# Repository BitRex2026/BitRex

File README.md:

Bitcoin Miner With 4 BM1373 Chips

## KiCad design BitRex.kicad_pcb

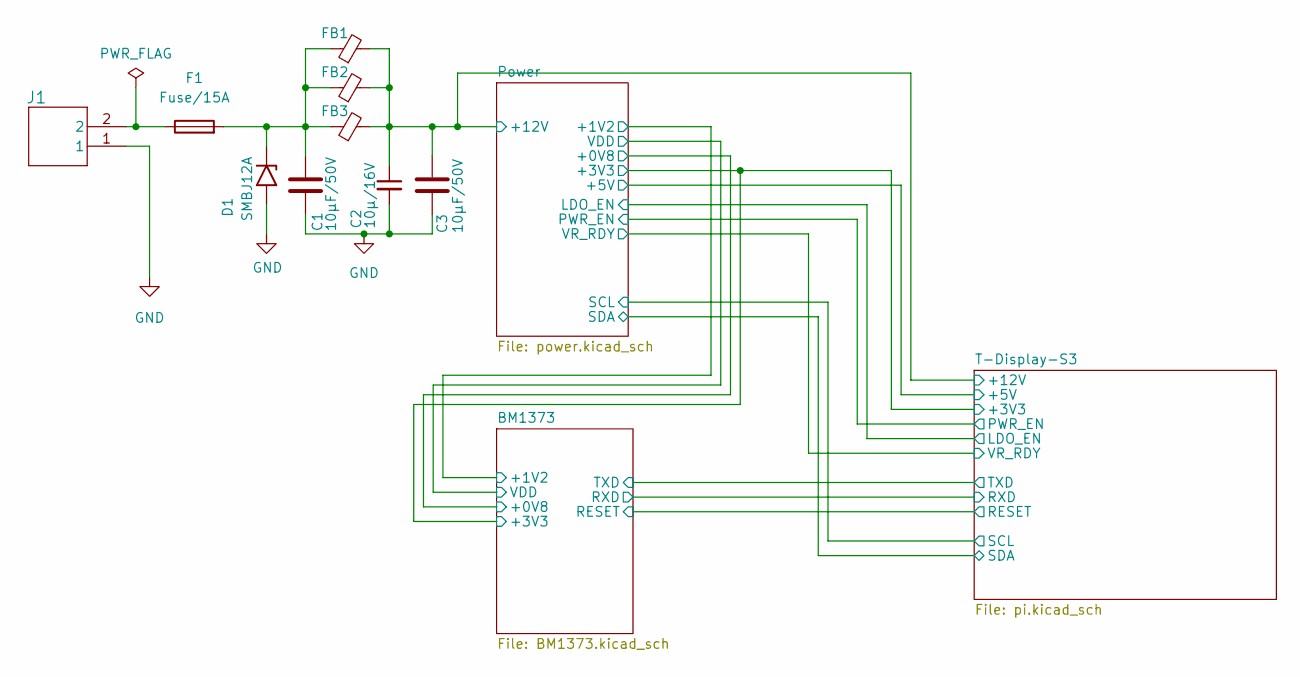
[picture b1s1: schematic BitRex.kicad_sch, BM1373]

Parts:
C1, C3: 10µF/50V; C_1206_3216Metric
C2: 10µ/16V; C_0603_1608Metric
D1: SMBJ12A; D_SMB; LCSC C113985
F1: Fuse/15A; Fuseholder_Blade_Mini_Keystone_3568
FB1, FB2, FB3: BLE32SN120SN1L; R_1210_3225Metric_Pad1.30x2.65mm_HandSolder; LCSC C5597997
J1: Connector 02x01; AMASS_XT60PW-M_1x02_P7.20mm_Horizontal; LCSC C98732

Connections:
+12V: C2.1, C3.1, FB1.2, FB2.2, FB3.2; also elsewhere on the board
GND: C1.2, C2.2, C3.2, D1.2 (A2), J1.1; also elsewhere on the board
unnamed: C1.1, D1.1 (A1), F1.2, FB1.1, FB2.1, FB3.1
unnamed: F1.1, J1.2

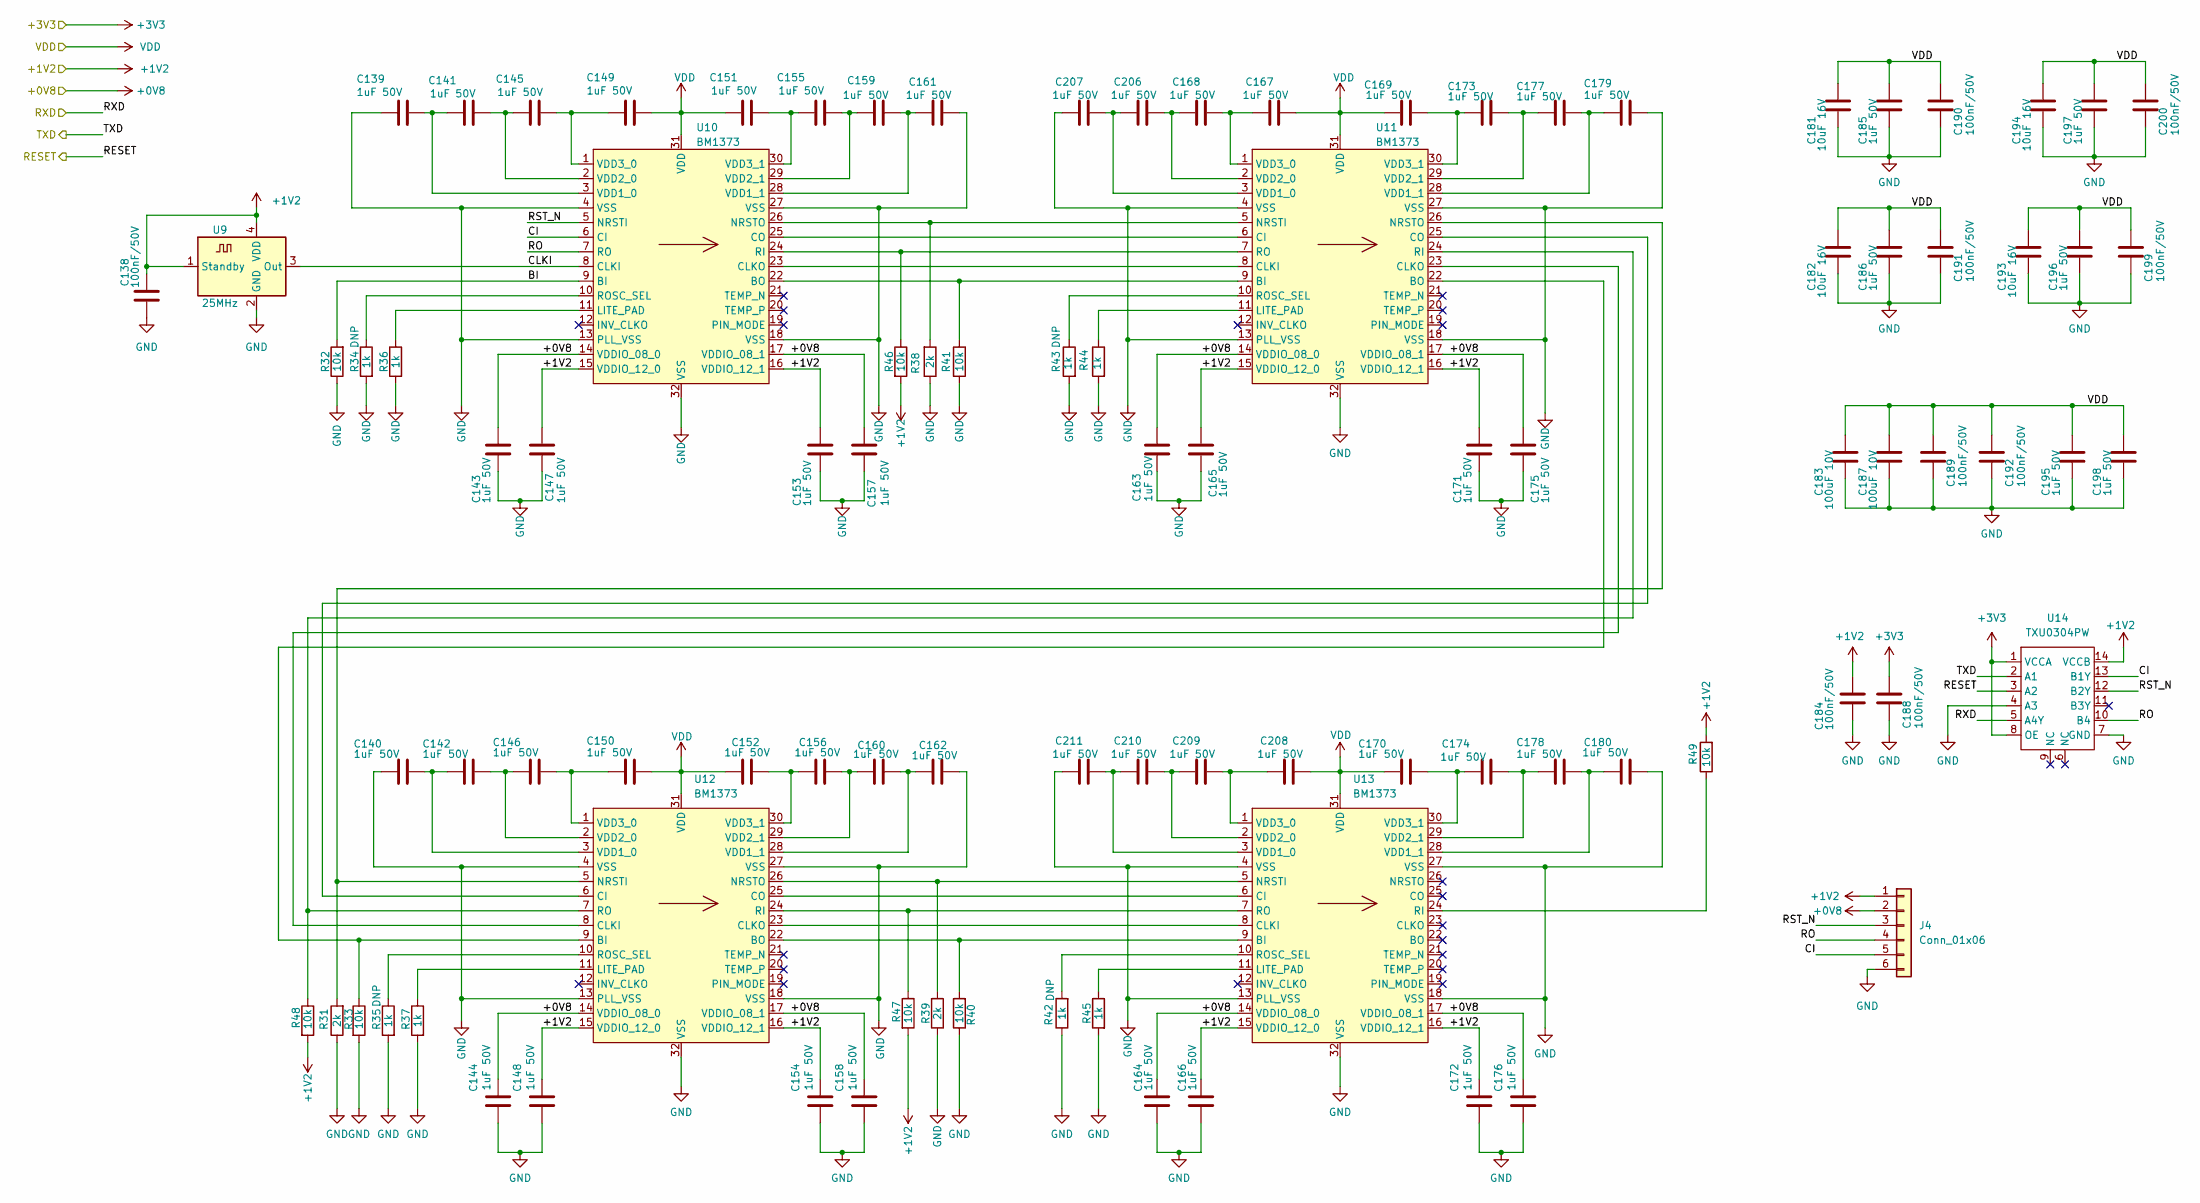
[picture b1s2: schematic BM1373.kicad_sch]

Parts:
C138, C184, C188, C189, C190, C191, C192, C199, C200: 100nF/50V; C_0805_2012Metric
C139, C140, C141, C142, C143, C144, C145, C146, C147, C148, C149, C150, C151, C152, C153, C154, C155, C156, C157, C158, C159, C160, C161, C162, C163, C164, C165, C166, C167, C168, C169, C170, C171, C172, C173, C174, C175, C176, C177, C178, C179, C180, C185, C186, C195, C196, C197, C198, C206, C207, C208, C209, C210, C211: 1uF 50V; C_0805_2012Metric
C181, C182, C193, C194: 10uF 16V; C_0805_2012Metric
C183, C187: 100uF 10V; C_1206_3216Metric
J4: Conn_01x06; PinHeader_1x06_P1.27mm_Vertical
R31, R38, R39: 2k; R_0603_1608Metric
R32, R33, R40, R41, R46, R47, R48, R49: 10k; R_0603_1608Metric
R34, R35, R36, R37, R42, R43, R44, R45: 1k; R_0603_1608Metric
U9: 25MHz; Oscillator_SMD_EuroQuartz_XO32-4Pin_3.2x2.5mm
U10, U11, U12, U13: BM1373; BM1373CC
U14: TXU0304PW; TSSOP-14_4.4x5mm_P0.65mm

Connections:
+0V8: C143.1, C144.1, C157.1, C158.1, C163.1, C164.1, C175.1, C176.1, J4.2, U10.14 (VDDIO_08_0), U10.17 (VDDIO_08_1), U11.14 (VDDIO_08_0), U11.17 (VDDIO_08_1), U12.14 (VDDIO_08_0), U12.17 (VDDIO_08_1), U13.14 (VDDIO_08_0), U13.17 (VDDIO_08_1); also elsewhere on the board
+1V2: C138.1, C147.1, C148.1, C153.1, C154.1, C165.1, C166.1, C171.1, C172.1, C184.1, J4.1, R46.2, R47.2, R48.2, R49.2, U9.1 (Standby), U9.4 (VDD), U10.15 (VDDIO_12_0), U10.16 (VDDIO_12_1), U11.15 (VDDIO_12_0), U11.16 (VDDIO_12_1), U12.15 (VDDIO_12_0), U12.16 (VDDIO_12_1), U13.15 (VDDIO_12_0), U13.16 (VDDIO_12_1), U14.14 (VCCB); also elsewhere on the board
+3V3: C188.1, U14.1 (VCCA), U14.8 (OE); also elsewhere on the board
/BM1373/BI: R32.2, U10.9 (BI)
/BM1373/CI: J4.5, U10.6 (CI), U14.13 (B1Y)
/BM1373/CLKI: U9.3 (Out), U10.8 (CLKI)
/BM1373/RESET: U14.3 (A2); also elsewhere on the board
/BM1373/RO: J4.4, U10.7 (RO), U14.10 (B4)
/BM1373/RST_N: J4.3, U10.5 (NRSTI), U14.12 (B2Y)
/BM1373/RXD: U14.5 (A4Y); also elsewhere on the board
/BM1373/TXD: U14.2 (A1); also elsewhere on the board
GND: C138.2, C139.1, C140.1, C143.2, C144.2, C147.2, C148.2, C153.2, C154.2, C157.2, C158.2, C161.2, C162.2, C163.2, C164.2, C165.2, C166.2, C171.2, C172.2, C175.2, C176.2, C179.2, C180.2, C181.1, C182.1, C183.1, C184.2, C185.1, C186.1, C187.1, C188.2, C189.2, C190.2, C191.2, C192.2, C193.1, C194.1, C195.1, C196.1, C197.1, C198.1, C199.2, C200.2, C207.1, C211.1, J4.6, R31.1, R32.1, R33.2, R34.2, R35.2, R36.2, R37.2, R38.1, R39.1, R40.1, R41.2, R42.1, R43.2, R44.2, R45.2, U9.2 (GND), U10.4 (VSS), U10.13 (PLL_VSS), U10.18 (VSS), U10.27 (VSS), U10.32 (VSS), U11.4 (VSS), U11.13 (PLL_VSS), U11.18 (VSS), U11.27 (VSS), U11.32 (VSS), U12.4 (VSS), U12.13 (PLL_VSS), U12.18 (VSS), U12.27 (VSS), U12.32 (VSS), U13.4 (VSS), U13.13 (PLL_VSS), U13.18 (VSS), U13.27 (VSS), U13.32 (VSS), U14.4 (A3), U14.7 (GND); also elsewhere on the board
unnamed: R41.1, U10.22 (BO), U11.9 (BI)
unnamed: U10.23 (CLKO), U11.8 (CLKI)
unnamed: U10.25 (CO), U11.6 (CI)
unnamed: R36.1, U10.11 (LITE_PAD)
unnamed: R38.2, U10.26 (NRSTO), U11.5 (NRSTI)
unnamed: R46.1, U10.24 (RI), U11.7 (RO)
unnamed: R34.1, U10.10 (ROSC_SEL)
unnamed: C139.2, C141.1, U10.3 (VDD1_0)
unnamed: C159.2, C161.1, U10.28 (VDD1_1)
unnamed: C141.2, C145.1, U10.2 (VDD2_0)
unnamed: C155.2, C159.1, U10.29 (VDD2_1)
unnamed: C145.2, C149.1, U10.1 (VDD3_0)
unnamed: C151.2, C155.1, U10.30 (VDD3_1)
unnamed: R33.1, U11.22 (BO), U12.9 (BI)
unnamed: U11.23 (CLKO), U12.8 (CLKI)
unnamed: U11.25 (CO), U12.6 (CI)
unnamed: R44.1, U11.11 (LITE_PAD)
unnamed: R31.2, U11.26 (NRSTO), U12.5 (NRSTI)
unnamed: R48.1, U11.24 (RI), U12.7 (RO)
unnamed: R43.1, U11.10 (ROSC_SEL)
unnamed: C206.1, C207.2, U11.3 (VDD1_0)
unnamed: C177.2, C179.1, U11.28 (VDD1_1)
unnamed: C168.1, C206.2, U11.2 (VDD2_0)
unnamed: C173.2, C177.1, U11.29 (VDD2_1)
unnamed: C167.1, C168.2, U11.1 (VDD3_0)
unnamed: C169.2, C173.1, U11.30 (VDD3_1)
unnamed: R40.2, U12.22 (BO), U13.9 (BI)
unnamed: U12.23 (CLKO), U13.8 (CLKI)
unnamed: U12.25 (CO), U13.6 (CI)
unnamed: R37.1, U12.11 (LITE_PAD)
unnamed: R39.2, U12.26 (NRSTO), U13.5 (NRSTI)
unnamed: R47.1, U12.24 (RI), U13.7 (RO)
unnamed: R35.1, U12.10 (ROSC_SEL)
unnamed: C140.2, C142.1, U12.3 (VDD1_0)
unnamed: C160.2, C162.1, U12.28 (VDD1_1)
unnamed: C142.2, C146.1, U12.2 (VDD2_0)
unnamed: C156.2, C160.1, U12.29 (VDD2_1)
unnamed: C146.2, C150.1, U12.1 (VDD3_0)
unnamed: C152.2, C156.1, U12.30 (VDD3_1)
unnamed: R45.1, U13.11 (LITE_PAD)
unnamed: R49.1, U13.24 (RI)
unnamed: R42.2, U13.10 (ROSC_SEL)
unnamed: C210.1, C211.2, U13.3 (VDD1_0)
unnamed: C178.2, C180.1, U13.28 (VDD1_1)
unnamed: C209.1, C210.2, U13.2 (VDD2_0)
unnamed: C174.2, C178.1, U13.29 (VDD2_1)
unnamed: C208.1, C209.2, U13.1 (VDD3_0)
unnamed: C170.2, C174.1, U13.30 (VDD3_1)
VDD: C149.2, C150.2, C151.1, C152.1, C167.2, C169.1, C170.1, C181.2, C182.2, C183.2, C185.2, C186.2, C187.2, C189.1, C190.1, C191.1, C192.1, C193.2, C194.2, C195.2, C196.2, C197.2, C198.2, C199.1, C200.1, C208.2, U10.31 (VDD), U11.31 (VDD), U12.31 (VDD), U13.31 (VDD); also elsewhere on the board

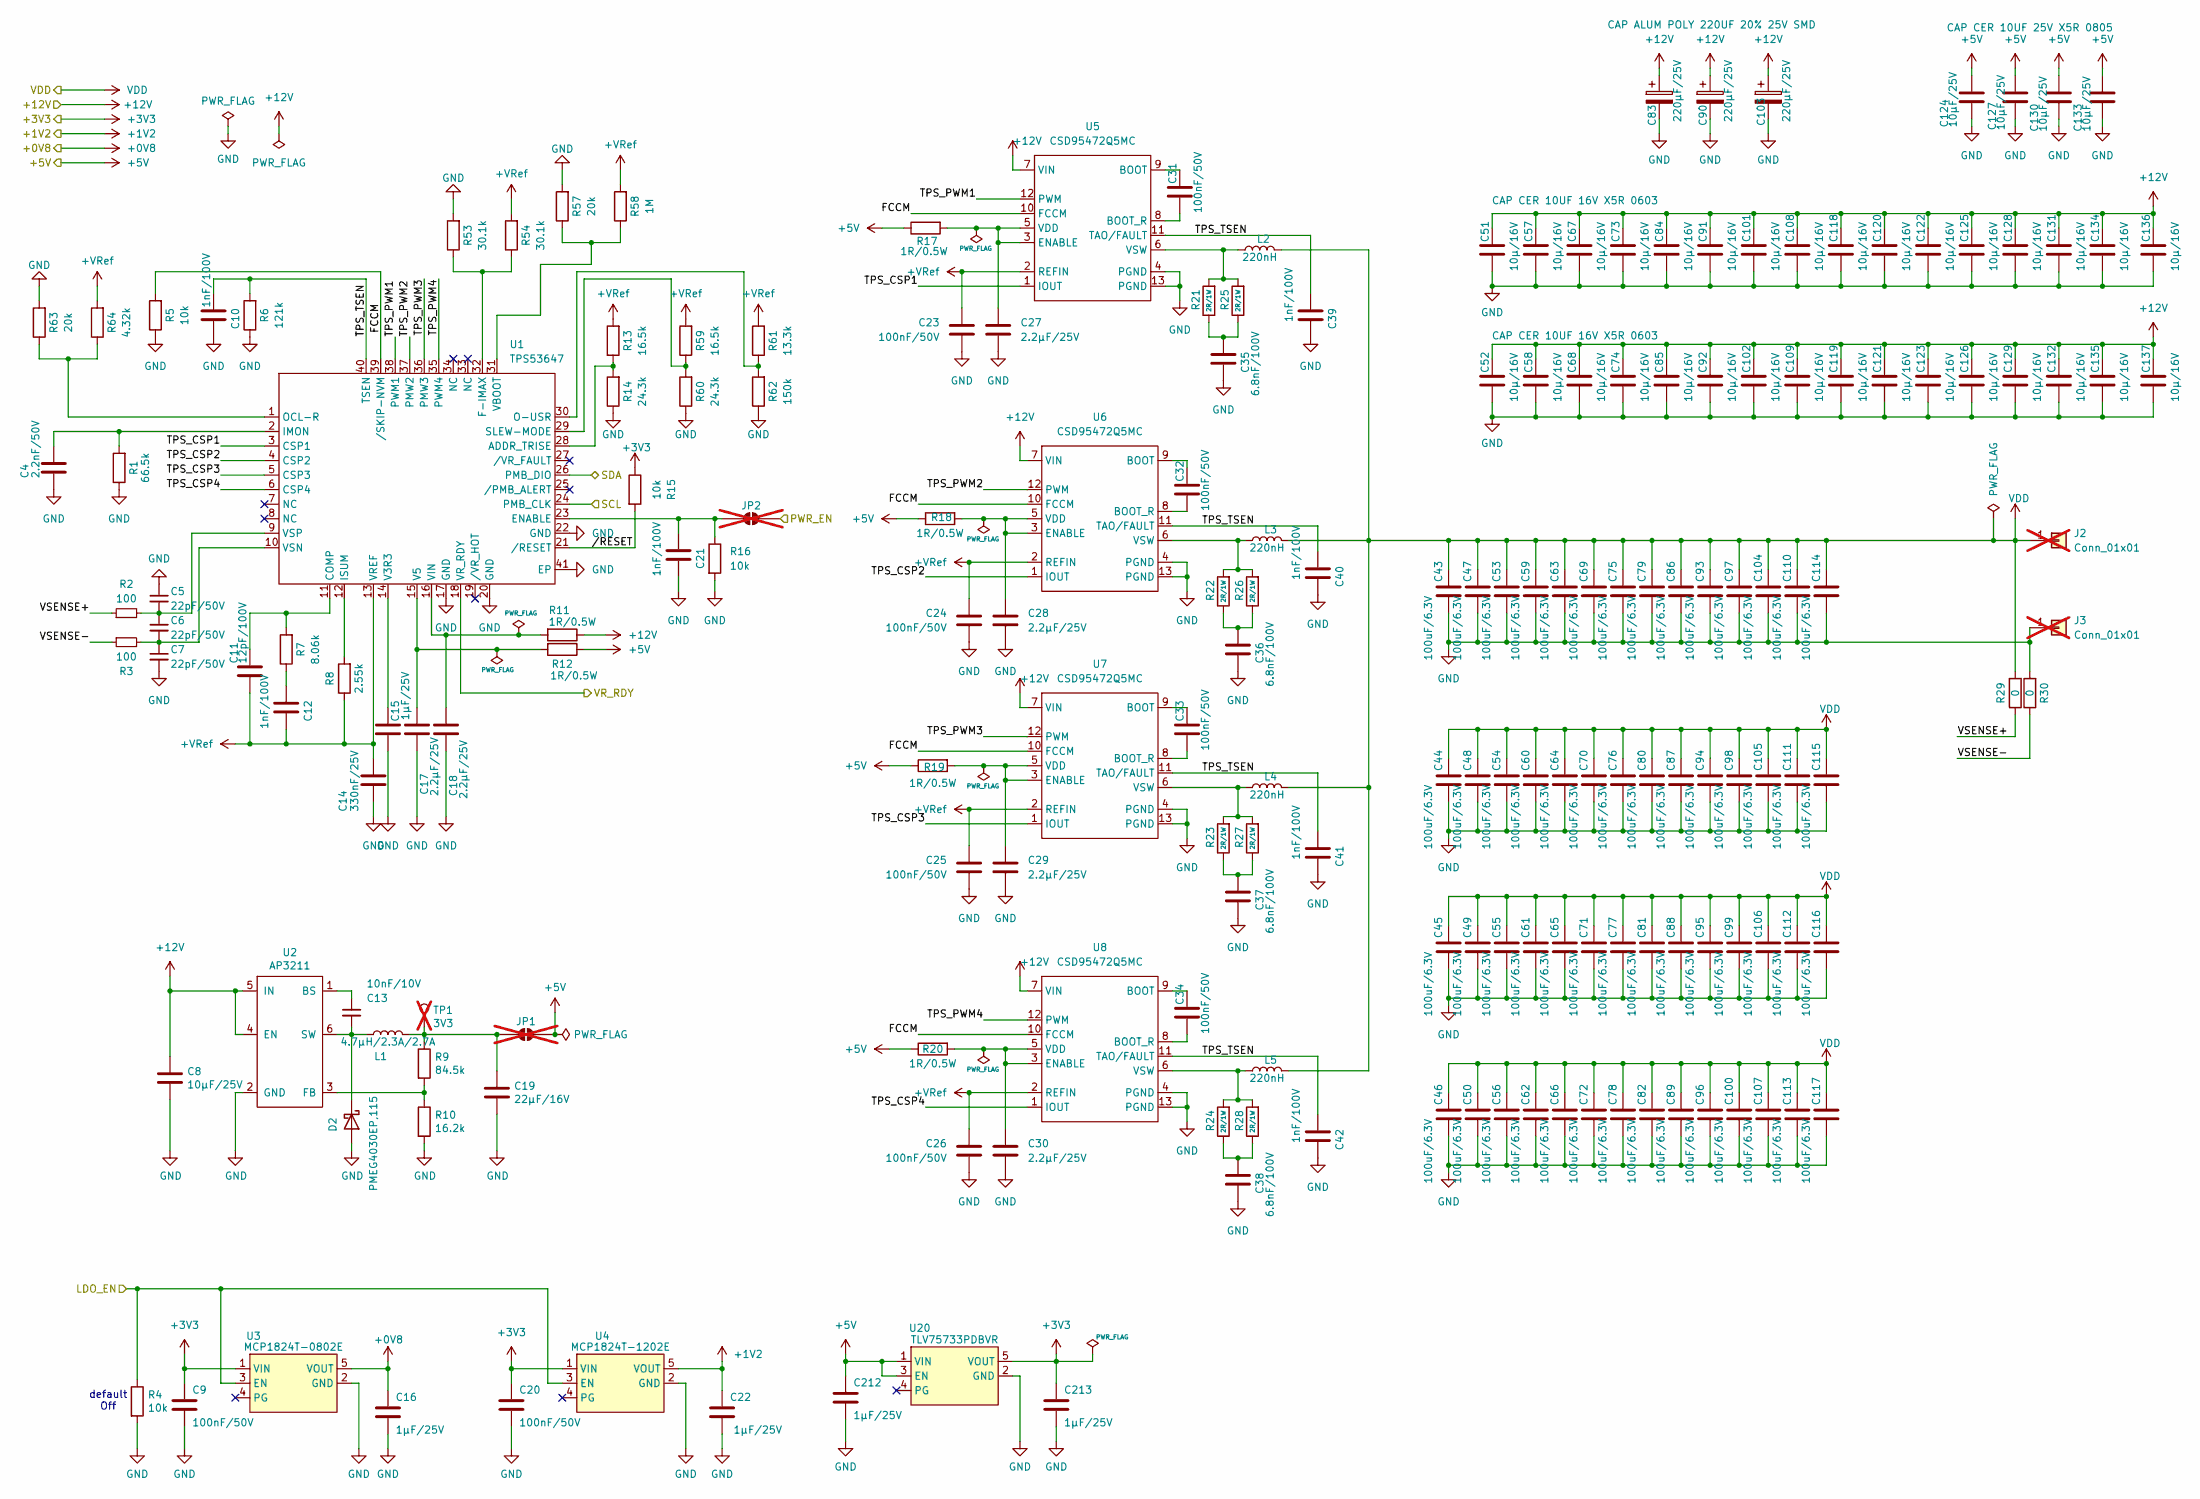
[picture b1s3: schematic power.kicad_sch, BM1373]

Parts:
C4: 2.2nF/50V; C_0805_2012Metric
C5, C6, C7: 22pF/50V; C_0603_1608Metric
C8, C124, C127, C130, C133: 10µF/25V; C_0805_2012Metric
C9, C20, C23, C24, C25, C26, C31, C32, C33, C34: 100nF/50V; C_0805_2012Metric
C10, C12, C21, C39, C40, C41, C42: 1nF/100V; C_0805_2012Metric
C11: 12pF/100V; C_0603_1608Metric
C13: 10nF/10V; C_0805_2012Metric
C14: 330nF/25V; C_0805_2012Metric
C15, C16, C22, C212, C213: 1µF/25V; C_0805_2012Metric
C17, C18, C27, C28, C29, C30: 2.2µF/25V; C_0805_2012Metric
C19: 22µF/16V; C_1206_3216Metric
C35, C36, C37, C38: 6.8nF/100V; C_0805_2012Metric
C43, C44, C45, C46, C47, C48, C49, C50, C53, C54, C55, C56, C59, C60, C61, C62, C63, C64, C65, C66, C69, C70, C71, C72, C75, C76, C77, C78, C79, C80, C81, C82, C86, C87, C88, C89, C93, C94, C95, C96, C97, C98, C99, C100, C104, C105, C106, C107, C110, C111, C112, C113, C114, C115, C116, C117: 100uF/6.3V; C_1206_3216Metric
C51, C52, C57, C58, C67, C68, C73, C74, C84, C85, C91, C92, C101, C102, C108, C109, C118, C119, C120, C121, C122, C123, C125, C126, C128, C129, C131, C132, C134, C135, C136, C137: 10µ/16V; C_0603_1608Metric; Part Number CL10A106MO8NQNC
C83, C90, C103: 220µF/25V; CP_Elec_8x10
D2: PMEG4030EP,115; D_SOD-128
J2, J3: Conn_01x01; Wuerth_REDCUBE-THR_WP-THRBU_74650194_THR; not fitted
JP1, JP2: SolderJumper_2_Open; SolderJumper-2_P1.3mm_Open_RoundedPad1.0x1.5mm; not fitted
L1: 4.7µH/2.3A/2.7A; L_Taiyo-Yuden_NR-50xx
L2, L3, L4, L5: 220nH; IFLR-4031GC-01-8x10
R1: 66.5k; R_0805_2012Metric
R2, R3: 100; R_0805_2012Metric
R4, R5, R15, R16: 10k; R_0805_2012Metric
R6: 121k; R_0805_2012Metric
R7: 8.06k; R_0805_2012Metric
R8: 2.55k; R_0805_2012Metric
R9: 84.5k; R_0805_2012Metric
R10: 16.2k; R_0805_2012Metric
R11, R12, R17, R18, R19, R20: 1R/0.5W; R_0805_2012Metric
R13, R59: 16.5k; R_0805_2012Metric
R14, R60: 24.3k; R_0805_2012Metric
R21, R22, R23, R24, R25, R26, R27, R28: 2R/1W; R_1206_3216Metric
R29, R30: 0; R_0805_2012Metric; LCSC C17477
R53, R54: 30.1k; R_0805_2012Metric
R57, R63: 20k; R_0805_2012Metric
R58: 1M; R_0805_2012Metric
R61: 13.3k; R_0805_2012Metric
R62: 150k; R_0805_2012Metric
R64: 4.32k; R_0805_2012Metric
TP1: 3V3; TestPoint_Pad_2.0x2.0mm; not fitted
U1: TPS53647; Texas_RHA0040B_VQFN-40-1EP_6x6mm_P0.5mm_EP4.15x4.15mm_Therm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
U2: AP3211; SOT-23-6
U3: MCP1824T-0802E; SOT-23-5
U4: MCP1824T-1202E; SOT-23-5
U5, U6, U7, U8: CSD95472Q5MC; CSD95472-SON-5x6
U20: TLV75733PDBVR; SOT-23-5

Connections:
+0V8: C16.1, U3.5 (VOUT); also elsewhere on the board
+1V2: C22.1, U4.5 (VOUT); also elsewhere on the board
+3V3: C9.1, C20.1, C213.1, R15.1, U3.1 (VIN), U4.1 (VIN), U20.5 (VOUT); also elsewhere on the board
+5V: C124.1, C127.1, C130.1, C133.1, C212.1, JP1.2 (B), R12.1, R17.1, R18.1, R19.1, R20.1, U20.1 (VIN), U20.3 (EN); also elsewhere on the board
+12V: C8.1, C51.1, C52.1, C57.1, C58.1, C67.1, C68.1, C73.1, C74.1, C83.1, C84.1, C85.1, C90.1, C91.1, C92.1, C101.1, C102.1, C103.1, C108.1, C109.1, C118.1, C119.1, C120.1, C121.1, C122.1, C123.1, C125.1, C126.1, C128.1, C129.1, C131.1, C132.1, C134.1, C135.1, C136.1, C137.1, R11.1, U2.4 (EN), U2.5 (IN), U5.7 (VIN), U6.7 (VIN), U7.7 (VIN), U8.7 (VIN); also elsewhere on the board
+VRef: C11.2, C12.2, C14.1, C23.1, C24.1, C25.1, C26.1, R8.1, R13.2, R54.2, R58.2, R59.2, R61.2, R64.2, U1.13 (VREF), U5.2 (REFIN), U6.2 (REFIN), U7.2 (REFIN), U8.2 (REFIN)
/Power/FCCM: R5.2, U1.39 (/SKIP-NVM), U5.10 (FCCM), U6.10 (FCCM), U7.10 (FCCM), U8.10 (FCCM)
/Power/LDO_EN: R4.1, U3.3 (EN), U4.3 (EN); also elsewhere on the board
/Power/PWR_EN: JP2.2 (B); also elsewhere on the board
/Power/TPS_CSP1: U1.3 (CSP1), U5.1 (IOUT)
/Power/TPS_CSP2: U1.4 (CSP2), U6.1 (IOUT)
/Power/TPS_CSP3: U1.5 (CSP3), U7.1 (IOUT)
/Power/TPS_CSP4: U1.6 (CSP4), U8.1 (IOUT)
/Power/TPS_PWM1: U1.38 (PWM1), U5.12 (PWM)
/Power/TPS_PWM2: U1.37 (PMW2), U6.12 (PWM)
/Power/TPS_PWM3: U1.36 (PMW3), U7.12 (PWM)
/Power/TPS_PWM4: U1.35 (PWM4), U8.12 (PWM)
/Power/TPS_TSEN: C10.1, C39.1, C40.1, C41.1, C42.1, R6.2, U1.40 (TSEN), U5.11 (TAO/FAULT), U6.11 (TAO/FAULT), U7.11 (TAO/FAULT), U8.11 (TAO/FAULT)
/Power/VR_RDY: U1.18 (VR_RDY); also elsewhere on the board
/Power/VSENSE+: R2.1, R29.1
/Power/VSENSE-: R3.1, R30.1
/Power//RESET: R15.2, U1.21 (/RESET)
/T-Display-S3/SCL: U1.24 (PMB_CLK); also elsewhere on the board
/T-Display-S3/SDA: U1.26 (PMB_DIO); also elsewhere on the board
GND: C4.2, C5.1, C7.2, C8.2, C9.2, C10.2, C14.2, C15.2, C16.2, C17.1, C18.1, C19.2, C20.2, C21.2, C22.2, C23.2, C24.2, C25.2, C26.2, C27.2, C28.2, C29.2, C30.2, C35.2, C36.2, C37.2, C38.2, C39.2, C40.2, C41.2, C42.2, C43.2, C44.2, C45.2, C46.2, C47.2, C48.2, C49.2, C50.2, C51.2, C52.2, C53.2, C54.2, C55.2, C56.2, C57.2, C58.2, C59.2, C60.2, C61.2, C62.2, C63.2, C64.2, C65.2, C66.2, C67.2, C68.2, C69.2, C70.2, C71.2, C72.2, C73.2, C74.2, C75.2, C76.2, C77.2, C78.2, C79.2, C80.2, C81.2, C82.2, C83.2, C84.2, C85.2, C86.2, C87.2, C88.2, C89.2, C90.2, C91.2, C92.2, C93.2, C94.2, C95.2, C96.2, C97.2, C98.2, C99.2, C100.2, C101.2, C102.2, C103.2, C104.2, C105.2, C106.2, C107.2, C108.2, C109.2, C110.2, C111.2, C112.2, C113.2, C114.2, C115.2, C116.2, C117.2, C118.2, C119.2, C120.2, C121.2, C122.2, C123.2, C124.2, C125.2, C126.2, C127.2, C128.2, C129.2, C130.2, C131.2, C132.2, C133.2, C134.2, C135.2, C136.2, C137.2, C212.2, C213.2, D2.2 (A), J3.1, R1.1, R4.2, R5.1, R6.1, R10.2, R14.1, R16.2, R30.2, R53.2, R57.2, R60.1, R62.1, R63.2, U1.17 (GND), U1.20 (GND), U1.22 (GND), U1.41 (EP), U2.2 (GND), U3.2 (GND), U4.2 (GND), U5.4 (PGND), U5.13 (PGND), U6.4 (PGND), U6.13 (PGND), U7.4 (PGND), U7.13 (PGND), U8.4 (PGND), U8.13 (PGND), U20.2 (GND); also elsewhere on the board
unnamed: C12.1, R7.1
unnamed: C35.1, R21.1, R25.1
unnamed: C36.1, R22.1, R26.1
unnamed: C37.1, R23.1, R27.1
unnamed: C38.1, R24.1, R28.1
unnamed: C13.2, D2.1 (K), L1.1, U2.6 (SW)
unnamed: C19.1, JP1.1 (A), L1.2, R9.1, TP1.1 (1_1)
unnamed: C21.1, JP2.1 (A), R16.1, U1.23 (ENABLE)
unnamed: R13.1, R14.2, U1.28 (ADDR_TRISE)
unnamed: C11.1, R7.2, U1.11 (COMP)
unnamed: R53.1, R54.1, U1.32 (F-IMAX)
unnamed: C4.1, R1.2, U1.2 (IMON)
unnamed: R8.2, U1.12 (ISUM)
unnamed: R61.1, R62.2, U1.30 (O-USR)
unnamed: R63.1, R64.1, U1.1 (OCL-R)
unnamed: R59.1, R60.2, U1.29 (SLEW-MODE)
unnamed: C15.1, U1.14 (V3R3)
unnamed: C17.2, R12.2, U1.15 (V5)
unnamed: R57.1, R58.1, U1.31 (VBOOT)
unnamed: C18.2, R11.2, U1.16 (VIN)
unnamed: C6.2, C7.1, R3.2, U1.10 (VSN)
unnamed: C5.2, C6.1, R2.2, U1.9 (VSP)
unnamed: C13.1, U2.1 (BS)
unnamed: R9.2, R10.1, U2.3 (FB)
unnamed: C31.1, U5.9 (BOOT)
unnamed: C31.2, U5.8 (BOOT_R)
unnamed: C27.1, R17.2, U5.3 (ENABLE), U5.5 (VDD)
unnamed: L2.1, R21.2, R25.2, U5.6 (VSW)
unnamed: C32.1, U6.9 (BOOT)
unnamed: C32.2, U6.8 (BOOT_R)
unnamed: C28.1, R18.2, U6.3 (ENABLE), U6.5 (VDD)
unnamed: L3.1, R22.2, R26.2, U6.6 (VSW)
unnamed: C33.1, U7.9 (BOOT)
unnamed: C33.2, U7.8 (BOOT_R)
unnamed: C29.1, R19.2, U7.3 (ENABLE), U7.5 (VDD)
unnamed: L4.1, R23.2, R27.2, U7.6 (VSW)
unnamed: C34.1, U8.9 (BOOT)
unnamed: C34.2, U8.8 (BOOT_R)
unnamed: C30.1, R20.2, U8.3 (ENABLE), U8.5 (VDD)
unnamed: L5.1, R24.2, R28.2, U8.6 (VSW)
VDD: C43.1, C44.1, C45.1, C46.1, C47.1, C48.1, C49.1, C50.1, C53.1, C54.1, C55.1, C56.1, C59.1, C60.1, C61.1, C62.1, C63.1, C64.1, C65.1, C66.1, C69.1, C70.1, C71.1, C72.1, C75.1, C76.1, C77.1, C78.1, C79.1, C80.1, C81.1, C82.1, C86.1, C87.1, C88.1, C89.1, C93.1, C94.1, C95.1, C96.1, C97.1, C98.1, C99.1, C100.1, C104.1, C105.1, C106.1, C107.1, C110.1, C111.1, C112.1, C113.1, C114.1, C115.1, C116.1, C117.1, J2.1, L2.2, L3.2, L4.2, L5.2, R29.2; also elsewhere on the board

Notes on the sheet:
default Off

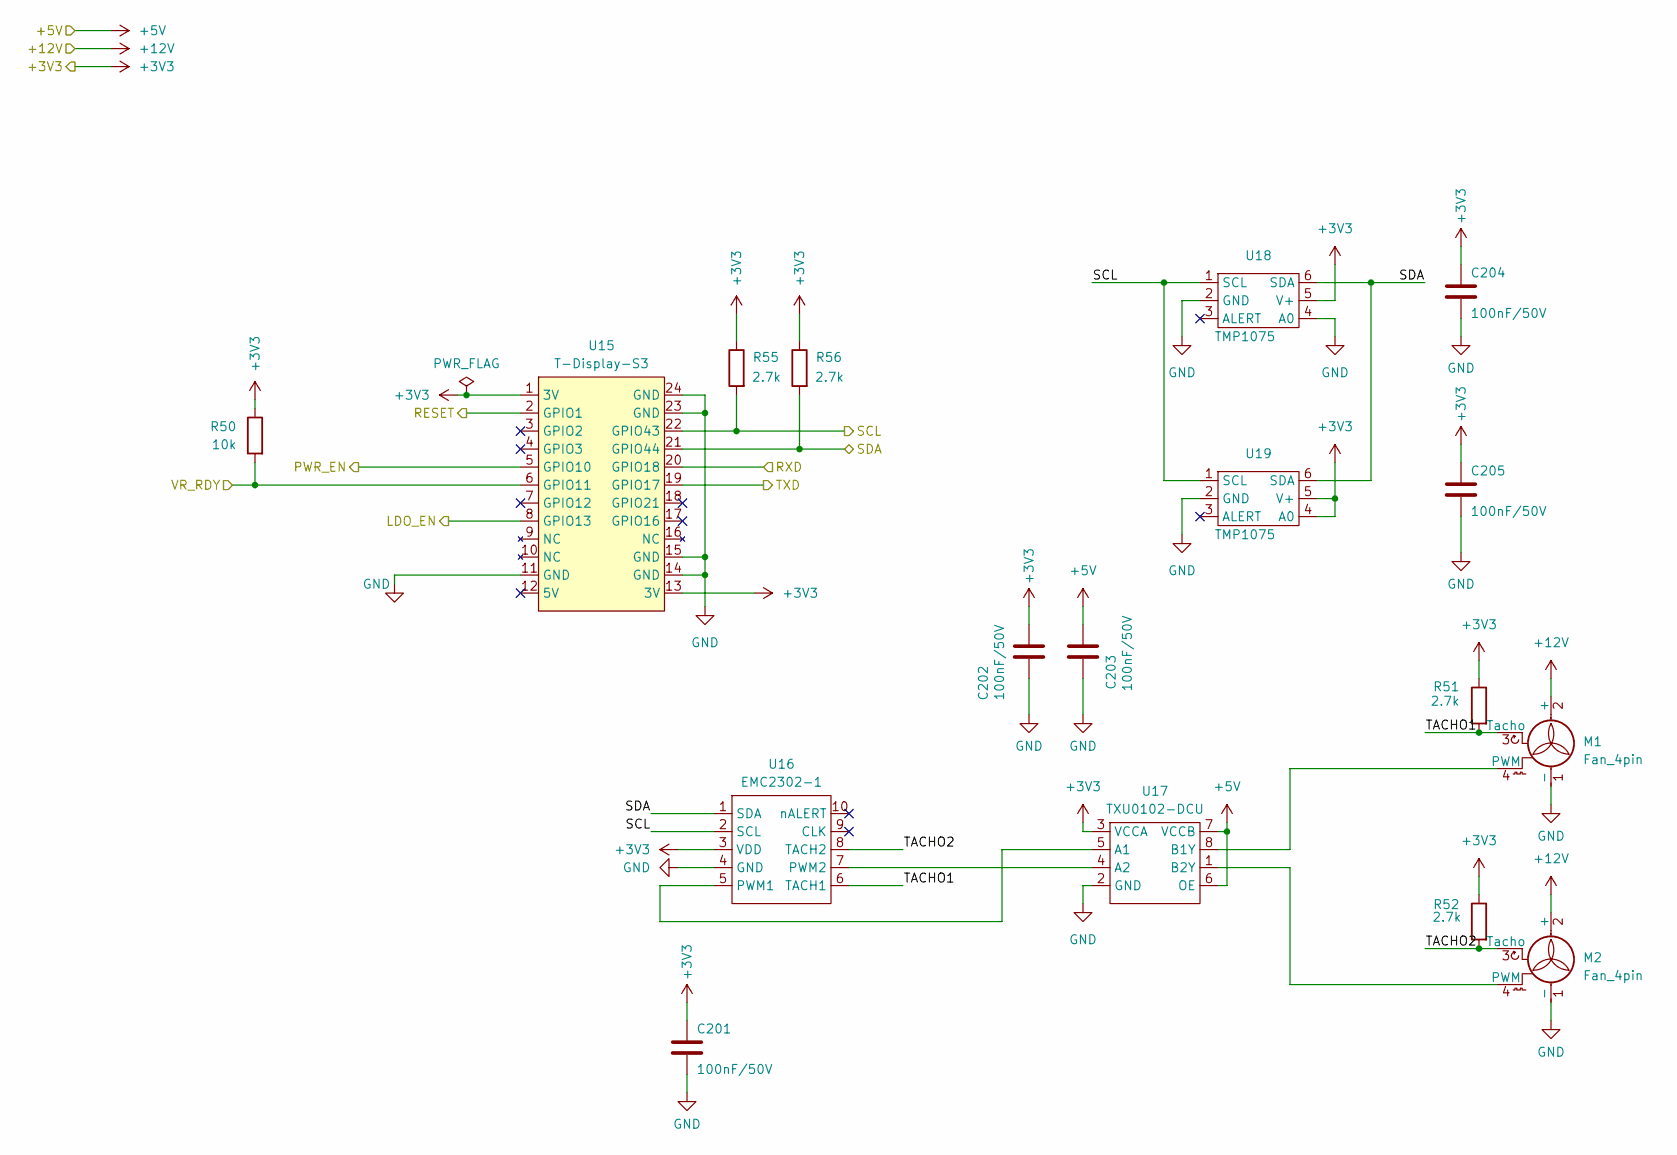
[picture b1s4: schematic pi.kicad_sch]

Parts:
C201, C202, C203, C204, C205: 100nF/50V; C_0805_2012Metric
M1, M2: Fan_4pin; FanPinHeader_1x04_P2.54mm_Vertical
R50: 10k; R_0805_2012Metric
R51, R52, R55, R56: 2.7k; R_0805_2012Metric
U15: T-Display-S3; PinSocket_T-DISPLAY-S3
U16: EMC2302-1; MSOP-10_3x3mm_P0.5mm
U17: TXU0102-DCU; VSSOP-8_2.3x2mm_P0.5mm
U18, U19: TMP1075; TMP1075-DRL

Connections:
+3V3: C201.1, C202.1, C204.1, C205.1, R50.1, R51.1, R52.1, R55.1, R56.1, U15.1 (3V), U15.13 (3V), U16.3 (VDD), U17.3 (VCCA), U18.5 (V+), U19.4 (A0), U19.5 (V+); also elsewhere on the board
+5V: C203.1, U17.6 (OE), U17.7 (VCCB); also elsewhere on the board
+12V: M1.2 (+), M2.2 (+); also elsewhere on the board
/BM1373/RESET: U15.2 (GPIO1); also elsewhere on the board
/BM1373/RXD: U15.20 (GPIO18); also elsewhere on the board
/BM1373/TXD: U15.19 (GPIO17); also elsewhere on the board
/Power/LDO_EN: U15.8 (GPIO13); also elsewhere on the board
/Power/PWR_EN: U15.5 (GPIO10); also elsewhere on the board
/Power/VR_RDY: R50.2, U15.6 (GPIO11); also elsewhere on the board
/T-Display-S3/SCL: R55.2, U15.22 (GPIO43), U16.2 (SCL), U18.1 (SCL), U19.1 (SCL); also elsewhere on the board
/T-Display-S3/SDA: R56.2, U15.21 (GPIO44), U16.1 (SDA), U18.6 (SDA), U19.6 (SDA); also elsewhere on the board
/T-Display-S3/TACHO1: M1.3 (Tacho), R51.2, U16.6 (TACH1)
/T-Display-S3/TACHO2: M2.3 (Tacho), R52.2, U16.8 (TACH2)
GND: C201.2, C202.2, C203.2, C204.2, C205.2, M1.1 (-), M2.1 (-), U15.11 (GND), U15.14 (GND), U15.15 (GND), U15.23 (GND), U15.24 (GND), U16.4 (GND), U17.2 (GND), U18.2 (GND), U18.4 (A0), U19.2 (GND); also elsewhere on the board
unnamed: M1.4 (PWM), U17.8 (B1Y)
unnamed: M2.4 (PWM), U17.1 (B2Y)
unnamed: U16.5 (PWM1), U17.5 (A1)
unnamed: U16.7 (PWM2), U17.4 (A2)

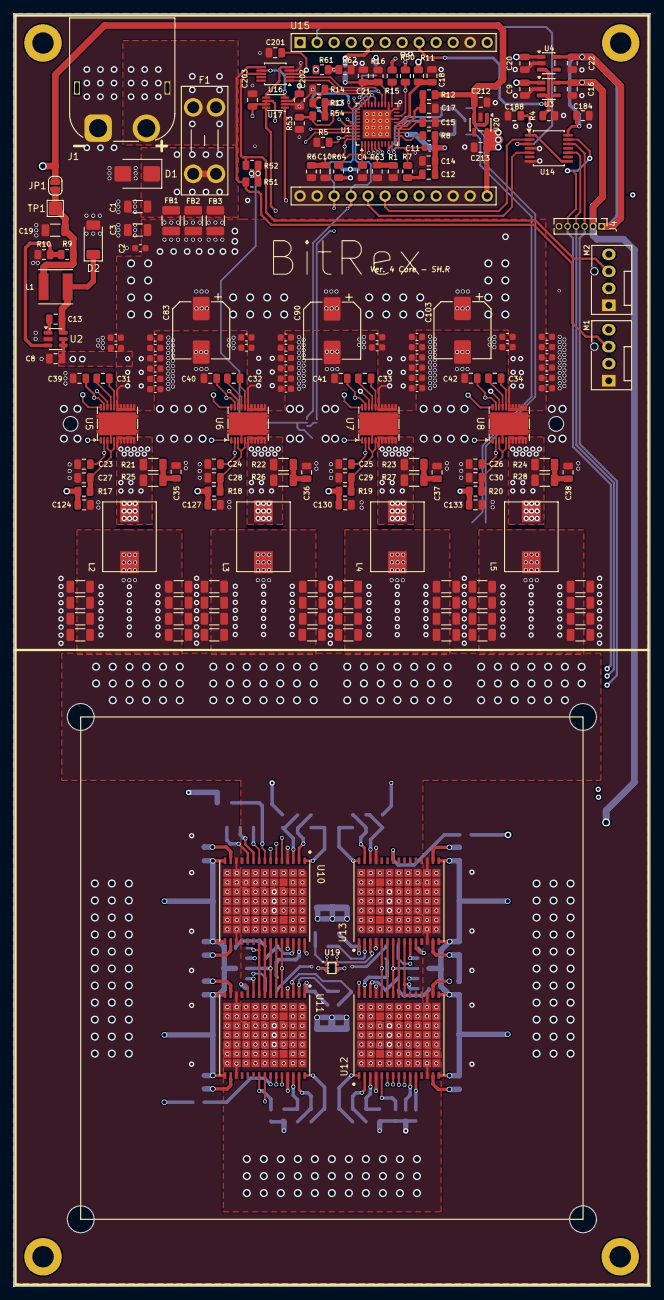
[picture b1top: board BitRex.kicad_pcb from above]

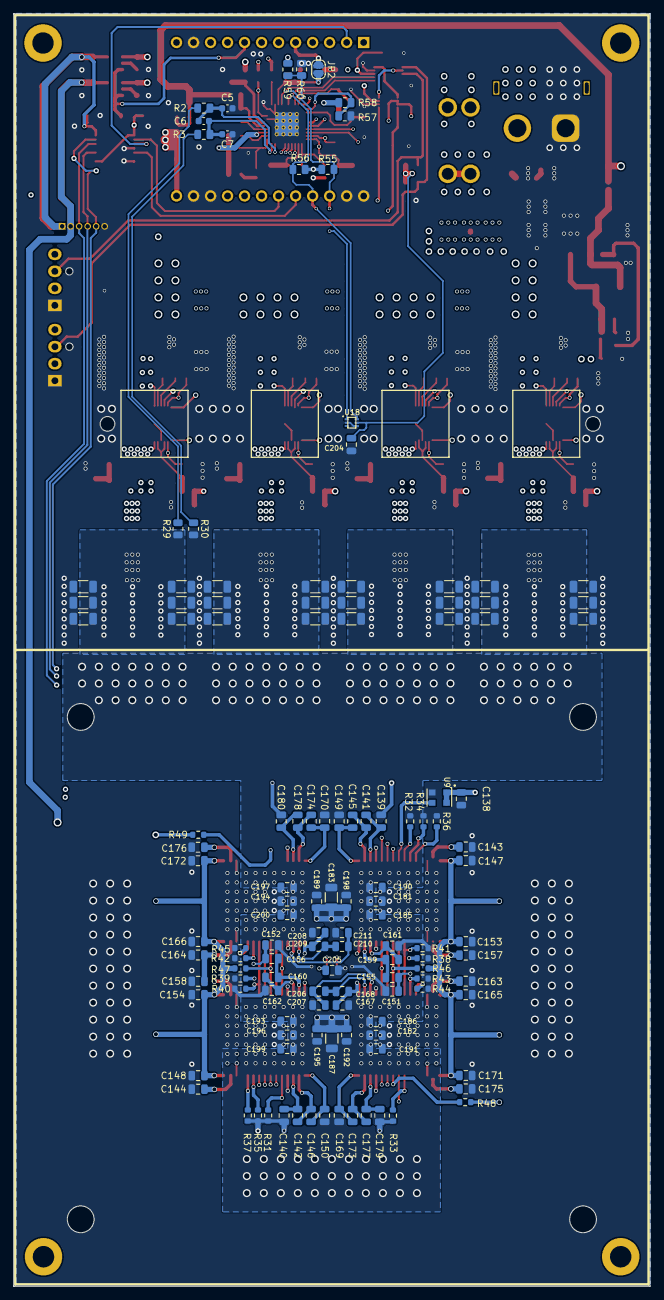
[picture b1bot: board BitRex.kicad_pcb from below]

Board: 6 copper layers, 95.0 x 190.0 mm, 315 parts (128 on the bottom side), 130 nets.

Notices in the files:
BM1373.kicad_sch:
Licensed under CERN-OHL-S v2
Copyright (c) 2026 BitRex2026
